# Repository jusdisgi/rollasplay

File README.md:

# rollasplay
Low profile 34-key split keyboard with a roller encoder and finger splay.

Layout created using ergogen. Please note the schematic is therefore not actually related to the PCB file, but they should match...should...

If you see problems PLEASE let me know...I am still very new at this. (a few more details after the pics...)

Once I validate and/or refine the design I hope to build it using direct-soldered Ambient Sunset silent tactile switches. I intend to SMD the diodes and controller on the front side of the board, then flip it and do the switches individually with a soldering iron.

If you're not familiar, this is the roller encoder in question: https://www.aliexpress.us/item/2251832804635444.html

They haven't been produced in a while so they're all new-old stock, and they keep getting pricier. But there's really nothing else around quite like them.

I got the XIAO Ergogen footprint from https://github.com/dohn-joh/emissary/tree/main/ergogen/footprints and removed the cutouts and through-holes for SMD.

Sadly the board is not reversable...the XIAO doesn't have symmetrical pins, and the surface mount doesn't allow for flipping it over. I will eventually make a right half. If you have ideas about better approaches to this problem please let me know.

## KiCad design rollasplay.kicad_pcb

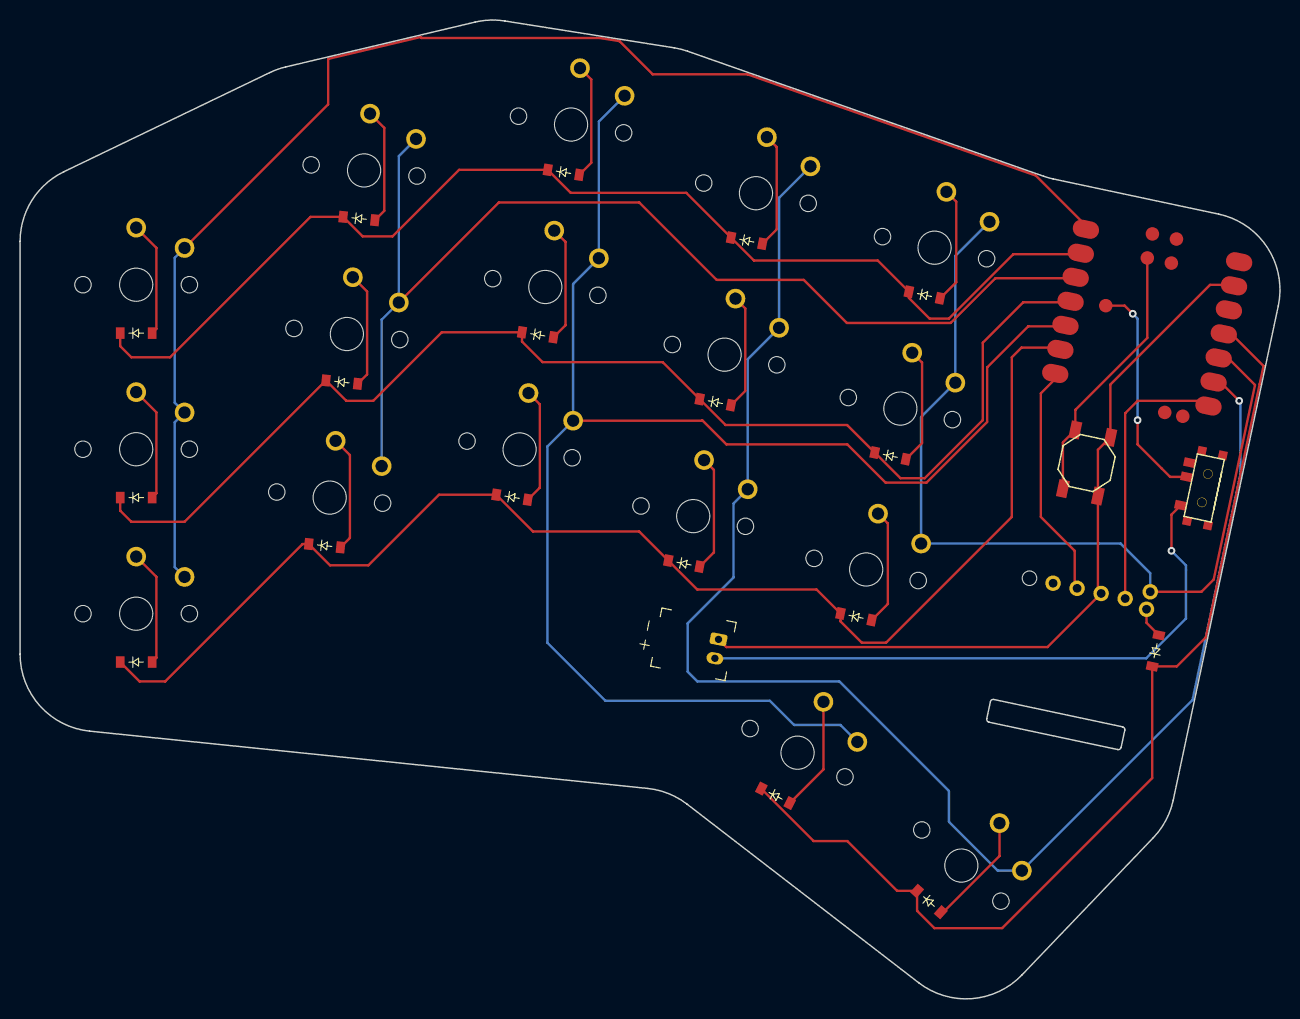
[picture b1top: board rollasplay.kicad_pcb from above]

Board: 2 copper layers, 130.2 x 101.2 mm, 39 parts (0 on the bottom side), 30 nets.

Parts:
B1: SW_TACT_ALPS_SKQGABE010
D1, D2, D3, D4, D5, D6, D7, D8, D9, D10, D11, D12, D13, D14, D15, D16, D17, D18: diode_tht_sod123
JST1: battery_connector_jst_ph_2
MCU1: xiao_smd
S1, S2, S3, S4, S5, S6, S7, S8, S9, S10, S11, S12, S13, S14, S15, S16, S17: PG1350
T1: SPDT_C128955

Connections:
BAT: MCU1.19, T1.2
BAT_P: JST1.2, T1.1
D0: MCU1.1, S1.1, S2.1, S3.1
D1: D3.1, D6.1, D9.1, D12.1, D15.1, MCU1.2
D2: MCU1.3, S4.1, S5.1, S6.1
D3: D2.1, D5.1, D8.1, D11.1, D14.1, MCU1.4
D4: MCU1.5, S7.1, S8.1, S9.1, S16.1
D5: D1.1, D4.1, D7.1, D10.1, D13.1, MCU1.6
D8: MCU1.9, S10.1, S11.1, S12.1, S17.1
D9: MCU1.10, S13.1, S14.1, S15.1
D10: D16.1, D17.1, D18.1, MCU1.11
GND: B1.1, JST1.1, MCU1.13
RST: B1.2, MCU1.17
index_bottom: D10.2, S10.2
index_home: D11.2, S11.2
index_top: D12.2, S12.2
inner_bottom: D13.2, S13.2
inner_home: D14.2, S14.2
inner_top: D15.2, S15.2
left_onerow: D16.2, S16.2
middle_bottom: D7.2, S7.2
middle_home: D8.2, S8.2
middle_top: D9.2, S9.2
pinky_bottom: D1.2, S1.2
pinky_home: D2.2, S2.2
pinky_top: D3.2, S3.2
right_onerow: D17.2, S17.2
ring_bottom: D4.2, S4.2
ring_home: D5.2, S5.2
ring_top: D6.2, S6.2

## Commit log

2025-04-08 Woops let's add files.
2025-04-08 Added Ergogen footprints dir.
2025-04-08 Update README.md
    Fixed pics
2025-04-08 Cleanup
